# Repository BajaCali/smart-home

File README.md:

# smart-home
SOČ 2019 about smart home concept and improoving it.

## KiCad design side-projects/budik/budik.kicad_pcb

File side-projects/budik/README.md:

# Budík
- uses ESP8266
- no beebs, only light
- 12 RGB LEDs - NeoPixels WS2812B
- 2 7_segment displays for seconds
- power from usb charger or 5V battry (recommended charger for LEDs and Wi-Fi)
- 3 buttons for some integration for future (one for alarm itself)

[parts](https://docs.google.com/spreadsheets/d/1WjRUrchE3KQip7q58ixRBthmBE3NxKdhlOc1AkZFzec/edit?usp=sharing)

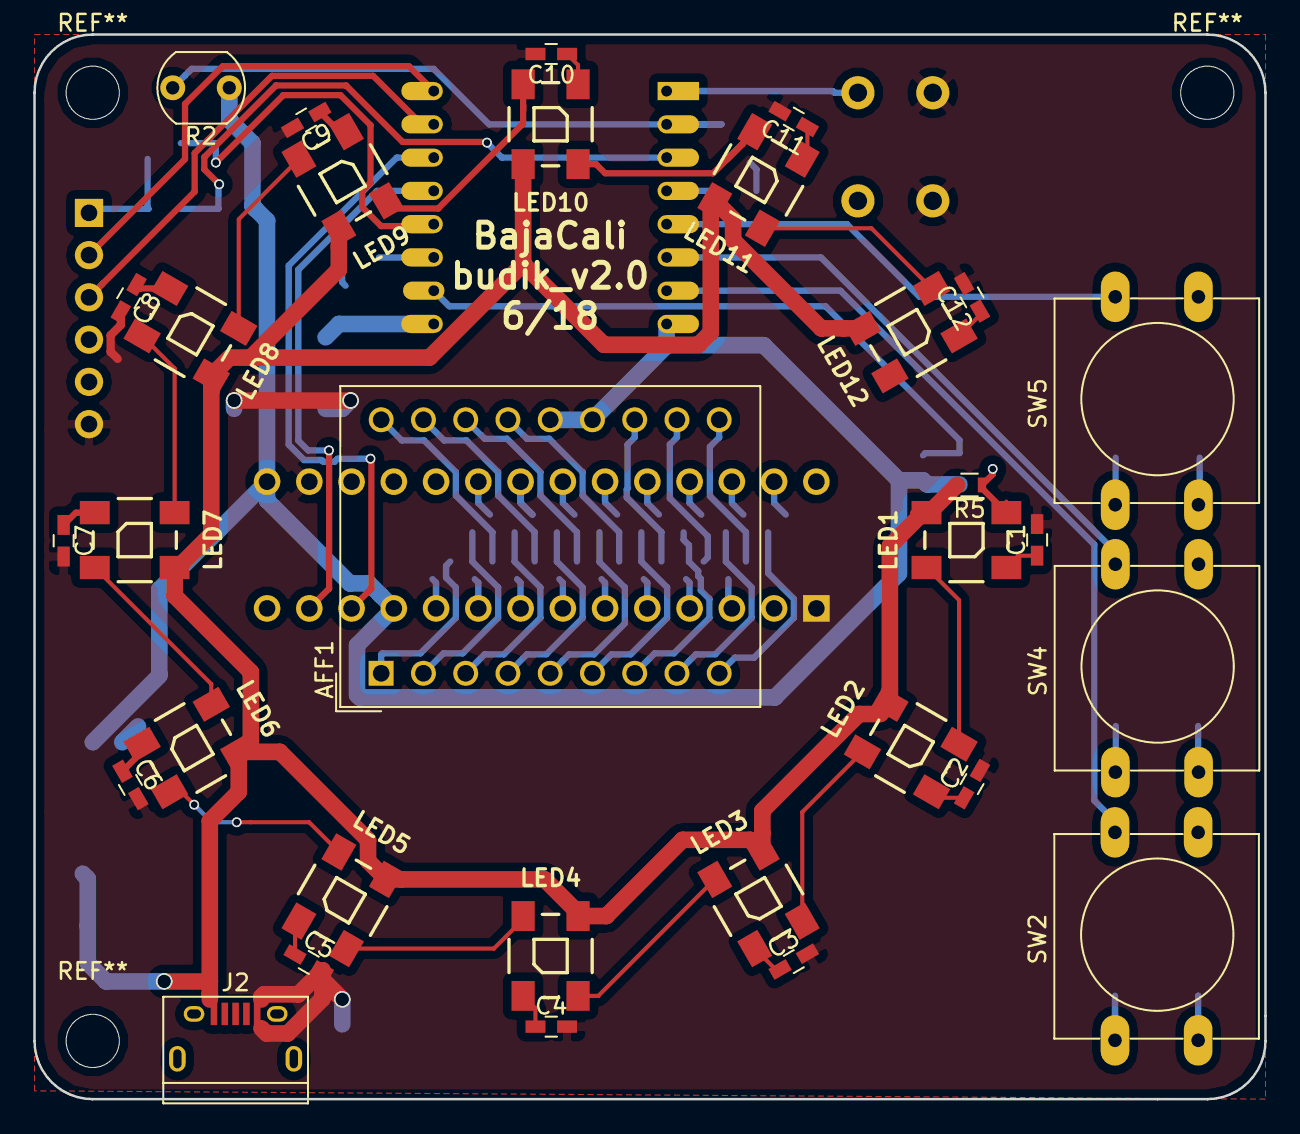
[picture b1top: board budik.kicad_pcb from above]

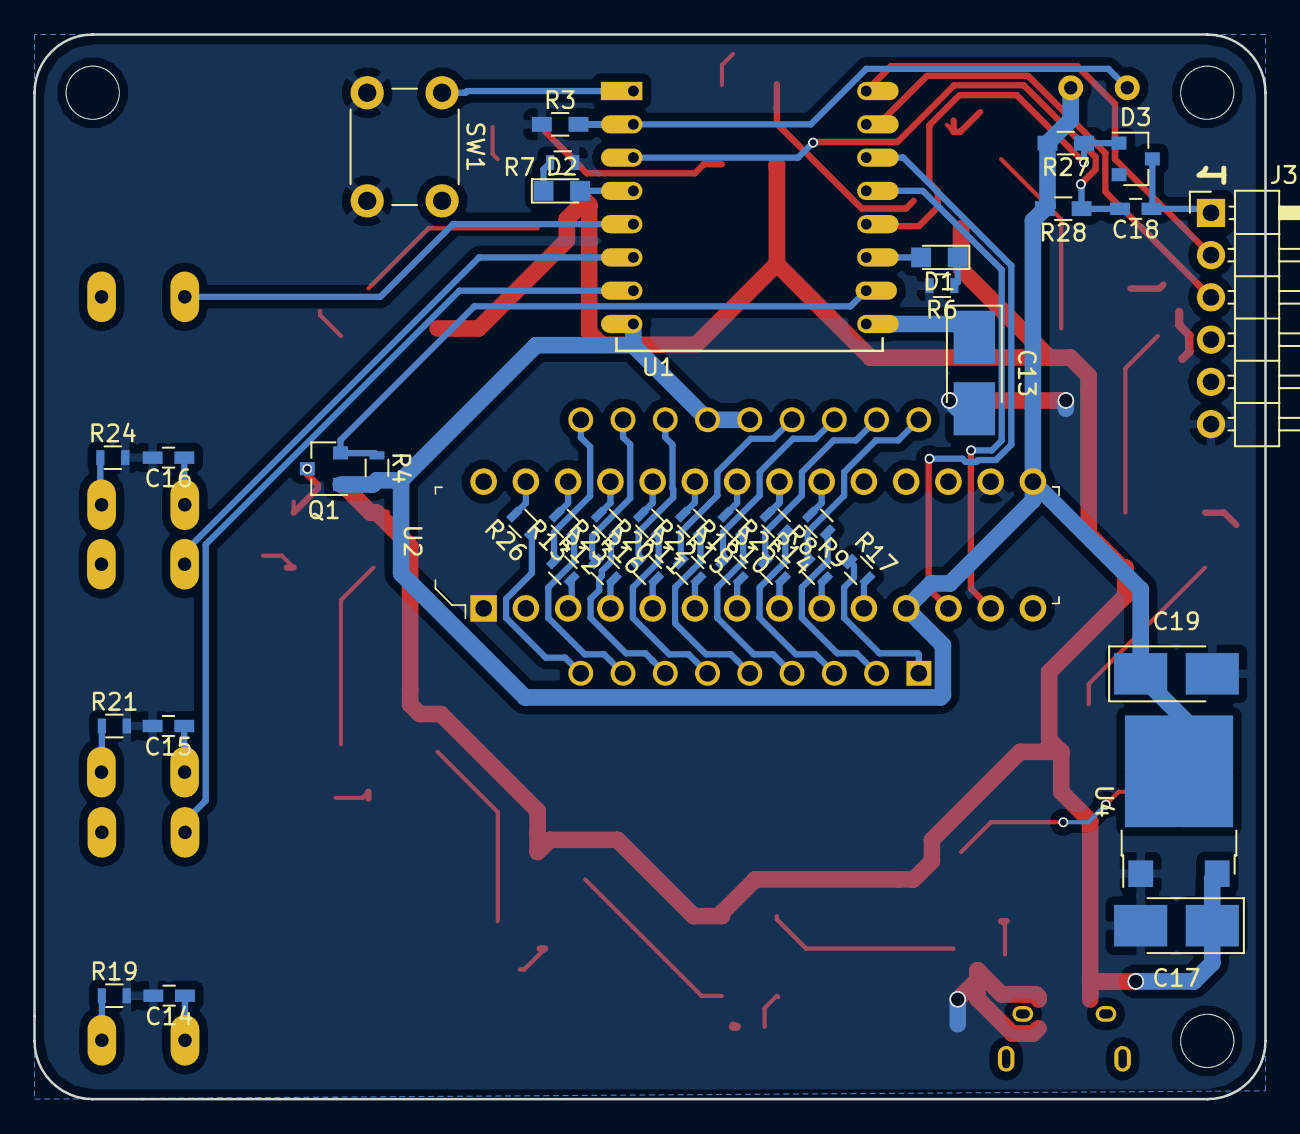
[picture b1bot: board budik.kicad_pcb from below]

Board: 2 copper layers, 74.0 x 64.0 mm, 72 parts (41 on the bottom side), 80 nets.

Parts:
AFF1: DC04-11_c; DA56-11CGKWA
C1, C2, C3, C4, C5, C6, C7, C8, C9, C10, C11, C12, C14, C15, C16, C18: 100n; C_0603_HandSoldering
C13, C17, C19: 10u; CP_Tantalum_Case-B_EIA-3528-21_Hand
D1, D2: LED; LED_0805
D3: D_x2_KCom_AAK; SOT-23
J2: USB_OTG; USB_Micro-B
J3: FTDI; Pin_Header_Angled_1x06_Pitch2.54mm
LED1, LED2, LED3, LED4, LED5, LED6, LED7, LED8, LED9, LED10, LED11, LED12: WS2812B
Q1: BSS138; SOT-23
R2: R_PHOTO; Resistor_LDR_5.1x4.3_RM3.4
R3: 300R; R_0603_HandSoldering
R4, R5: 10k; R_0603
R6, R7: 150R; R_0603
R8, R9, R10, R11, R12, R13, R14, R15, R16, R17, R18, R20, R22, R23, R25, R26: 100R; R_0603
R19, R21, R24: 4k7; R_0603
R27, R28: 10k; R_0603_HandSoldering
SW1: SW_DPST; SW_PUSH_6mm
SW2, SW4, SW5: SW_DPST; SW_PUSH-12mm
U1: ESP-12
U2: MCP23018-E_SP; DIP-28_W7.62mm
U4: LD1117S33CTR; ATPAK-2

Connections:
+3V3: AFF1.17, C19.1, Q1.1, R2.1, R4.2, R27.2, R28.2, U1.8, U2.11, U2.15, U4.2
+5V: C17.1, J2.1, LED1.1, LED2.1, LED3.1, LED4.1, LED5.1, LED6.1, LED7.1, LED8.1, LED9.1, LED10.1, LED11.1, LED12.1, R5.2, U4.3
Bt1: C14.1, SW2.1, U1.7
Bt2: C15.1, SW4.1, U1.6
Bt3: C16.1, SW5.1, U1.5
BtR: SW1.1, U1.1
CH_PD: C18.2, R28.1, U1.3
DATA_LED: Q1.2, R4.1, U1.10
DATA_LED_5V: LED1.4, Q1.3, R5.1
DIS_SCL: U1.14, U2.12
DIS_SDA: U1.13, U2.13
GND: C1.2, C2.2, C3.2, C4.2, C5.2, C6.2, C7.2, C8.2, C9.2, C10.2, C11.2, C12.2, C13.2, C14.2, C15.2, C16.2, C17.2, C19.2, J2.5, J3.6, R3.1, R6.2, R7.2, R19.2, R21.2, R24.2, SW1.2, U2.1, U2.16, U4.1
GPIO0: D3.1, R27.1, U1.12
L1: D2.2, U1.4
L2: D1.2, U1.11
unnamed: AFF1.1, R23.1
unnamed: AFF1.2, R26.1
unnamed: AFF1.3, R25.1
unnamed: AFF1.4, R22.1
unnamed: AFF1.5, R17.1
unnamed: AFF1.6, R14.1
unnamed: AFF1.7, R10.1
unnamed: AFF1.8, R9.1
unnamed: AFF1.9, R15.1
unnamed: AFF1.10, R16.1
unnamed: AFF1.11, R11.1
unnamed: AFF1.12, R12.1
unnamed: AFF1.13, R20.1
unnamed: AFF1.14, R13.1
unnamed: AFF1.15, R18.1
unnamed: AFF1.16, R8.1
unnamed: C1.1, LED1.3
unnamed: C2.1, LED2.3
unnamed: C3.1, LED3.3
unnamed: C4.1, LED4.3
unnamed: C5.1, LED5.3
unnamed: C6.1, LED6.3
unnamed: C7.1, LED7.3
unnamed: C8.1, LED8.3
unnamed: C9.1, LED9.3
unnamed: C10.1, LED10.3
unnamed: C11.1, LED11.3
unnamed: C12.1, LED12.3
unnamed: C13.1, U1.9
unnamed: C18.1, D3.3, J3.1
unnamed: D1.1, R6.1
unnamed: D2.1, R7.1
unnamed: LED1.2, LED2.4
unnamed: LED2.2, LED3.4
unnamed: LED3.2, LED4.4
unnamed: LED4.2, LED5.4
unnamed: LED5.2, LED6.4
unnamed: LED6.2, LED7.4
unnamed: LED7.2, LED8.4
unnamed: LED8.2, LED9.4
unnamed: LED10.2, LED11.4
unnamed: LED9.2, LED10.4
unnamed: LED11.2, LED12.4
unnamed: R8.2, U2.27
unnamed: R9.2, U2.9
unnamed: R10.2, U2.7
unnamed: R11.2, U2.5
unnamed: R12.2, U2.3
unnamed: R13.2, U2.26
unnamed: R14.2, U2.8
unnamed: R15.2, U2.6
unnamed: R16.2, U2.4
unnamed: R17.2, U2.10
unnamed: R18.2, U2.25
unnamed: R19.1, SW2.2
unnamed: R20.2, U2.24
unnamed: R21.1, SW4.2
unnamed: R22.2, U2.23
unnamed: R23.2, U2.22
unnamed: R24.1, SW5.2
unnamed: R25.2, U2.21
unnamed: R26.2, U2.20
PHOTO: R2.2, R3.2, U1.2
RX: J3.3, U1.15
TX: J3.2, U1.16

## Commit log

2018-04-20 Add text
2018-04-20 Format code of table.
2018-05-20 Initial commit.
2018-05-20 Some perhaps final changes in scheme, add parts
2018-05-28 Inited pcb, add led_placement.py
2018-05-29 Adapt led_placement to a new version of API
2018-05-29 Arrange LEDs using the script
2018-05-30 Add some pcb parts
2018-05-30 Draw most of parts (only power missing).
2018-06-02 Finish PCB v_1.0.
2018-06-03 Remake PCB into something like square
2018-06-05 Move voltage regulator further from the board margin
2018-11-04 Add GAP projects (Tx with ISR, Rx with LED)
2019-01-16 Add BT_blink project.
2019-01-16 Add delay func.
2019-01-21 Remanage dics
2019-01-22 Make Vypinac advertising and Spinac scaning
2019-01-23 Change ESP Spinac to scan countinously
2019-01-25 Set Vypinac to change man_data when switched external switch
2019-02-07 Add code for reading man_data and changing pin level by firstr byte of data (not working)
2019-02-11 Let one divece blink a led depending on input on another device
2019-02-12 Code clean and make more durable
2019-02-12 Clean code.
